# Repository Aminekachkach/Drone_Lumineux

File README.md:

[![Contributors][contributors-shield]][contributors-url]
[![LinkedIn][linkedin-shield]][linkedin-url]
[![LinkedIn2][linkedin-shield2]][linkedin-url2]

<!-- PROJECT LOGO -->
<br />
<div align="center">

<h3 align="center">Drone Lumineux</h3>

  <p align="center">
    A magic drone
</div>

<!-- TABLE OF CONTENTS -->
<details>
  <summary>Table des matières</summary>
  <ol>
    <li>
      <a href="#Introduction">Introduction</a>
      <ul>
        <li><a href="#organigramme-des-tâches-du-projet">Organigramme des tâches du projet</a </li>
        <li><a href="#architecture-générale">Architecture générale</a </li>
      </ul>
    </li>
    <li>
      <a href="#built-with">Build with</a>
    </li>
    <li>
      <a href="#test-initaire">Test Unitaire</a>
    <ul>
        </li><a href="#ESC">ESC</a></li>
        <li><a href="#MPU6050">MPU6050</a></li>
        <li><a href="#Neopixel">Neopixel</a></li>
    </ul>

  </ol>
</details>

## Introduction  
Le projet Drone Lumineux vise à concevoir un drone équipé d'un jeu de lumières. L'objectif est de créer une expérience visuelle unique en combinant les fonctionnalités d'un drone avec des effets lumineux spectaculaires.

Pour cela,  nous avons établi notre projet en utilisant une approche agile avec Scrum et les concepts d'épique (epic), de fonctionnalité (feature) et d'histoire utilisateur (user story). 

## Built With

* [![C][C.js]][C-url]
* [![Cube][Cube.js]][Cube-url]

### Organigramme des tâches du projet

En utilisant le modèle, nous avons identifié et défini les tâches qui correspondent aux histoires utilisateurs. L'objectif est de fournir rapidement de la valeur à notre produit en travaillant sur ces tâches de manière itérative. 
 
### Architecture générale

Après avoir effectué la sélection des composants et défini l'architecture générale de notre PCB , nous avons choisi d'utiliser deux contrôleurs différents : le microcontrôleur Nucleo STM32L412KB et le SoC QuickLogic Quick Feather EOS S3. L'objectif était de déterminer le contrôleur qui serait le plus adapté à notre configuration spécifique.
Cependant, lors du processus de développement, une mauvaise manipulation a entraîné un dysfonctionnement du bootloader du SoC, le rendant inutilisable (brické). Cette situation a nécessité d'abandonner l'utilisation du SoC Quick Feather EOS S3 pour notre projet.

[Drone_board_STM32_PCB](https://github.com/Aminekachkach/Drone_Lumineux/tree/main/hardware/Drone_board)

## Test Unitaire
Dans notre projet, nous utilisons des tests unitaires pour vérifier le bon fonctionnement de chaque composant, module et fonctionnalité du code. Les principaux éléments soumis à ces tests sont le driver ESC, le Nopixel et le MPU6050, ainsi que des fonctionnalités spécifiques telles que la configuration des broches PWM et la lecture des données du gyromètre.

### ESC

[Code Moteur](https://github.com/Aminekachkach/Drone_Lumineux/blob/main/firmware/drone/Core/Src/main_moteur.c)

Le driver ESC est spécifiquement conçu pour contrôler les moteurs brushless à courant continu (BLDC). Il reçoit en entrée un signal de modulation de largeur d'impulsion (PWM) qui permet de commander les phases du moteur. Dans notre application, nous utilisons des kits ESC+Moteurs fournis par miniplanes.

Sur le microcontrôleur Nucleo-STM32L412KB, nous allouons 4 broches qui sont connectées à la même chaîne PWM1 afin d'assurer la synchronisation.

PA8  ->  Broche PWM1-1

PA9  ->  Broche PWM1-2

PA10 ->  Broche PWM1-3

PA11 ->  Broche PWM1-4

Le driver fonctionne en configurant un signal PWM avec une période de 20 ms. Le rapport cyclique est ajusté pour envoyer des signaux de 1 ms pour l'initialisation, 1,5 ms pour une vitesse moyenne et 2 ms pour la vitesse maximale. Cela signifie qu'une variation de 1 ms à 2 ms fera tourner les moteurs de la vitesse minimale à la vitesse maximale.

Dans notre code, nous  générons les signaux PWM pour les 4 sorties, nous définissons trois constantes de vitesse : Rapport_cyclique_Min, Rapport_cyclique_securite et Rapport_cyclique_Max. À l'aide d'une boucle for, nous faisons varier la vitesse en utilisant les constantes Rapport_cyclique_Min et Rapport_cyclique_securite pour augmenter progressivement la vitesse des moteurs jusqu'à une vitesse raisonnable.

### MPU6050
[Code MPU](https://github.com/Aminekachkach/Drone_Lumineux/blob/main/firmware/drone/Core/Src/main_mpu.c)

Le MPU6050 est un composant qui combine un gyroscope et un accéléromètre à trois axes. Il est utilisé pour mesurer l'orientation, la rotation et l'accélération. Il utilise une communication I2C pour interagir avec notre microcontroleur STM32, nous allouons deux broches spécifiques pour établir la communication I2C avec les broches suivantes :

PA7  ->  Broche SCL

PB5  ->  Broche SDA

Au niveau du code, il existe une subtilité importante qui consiste à définir l'adresse du composant shiftée de 1 (0x68 << 1). Cela est nécessaire pour assurer une communication réussie entre le module et le microcontrôleur.

Avant de commencer la configuration, nous effectuons une vérification en interrogeant le registre "Who_am_i" à l'adresse 0x75. Cette étape nous permet de nous assurer que le module communique correctement avec le microcontrôleur. Si la communication est établie, le registre renverra la valeur 0x68.

Ensuite, nous procédons à la configuration de l'horloge interne à 8 MHz en utilisant le registre "Power management" situé à l'adresse 0x6B. Nous lui attribuons la valeur 0x00 pour sélectionner notre horloge souhaitée.

Nous appliquons également un filtre passe-bas avec une fréquence de coupure de 1 kHz afin d'éliminer les bruits qui pourraient perturber le fonctionnement du composant. Ce filtre est configuré en utilisant le registre situé à l'adresse 0x1A. Nous lui attribuons la valeur 0x05, ce qui correspond à une bande passante de 10 Hz.

Passons maintenant à la configuration du gyromètre en manipulant le registre "Gyro_Config" du MPU6050, situé à l'adresse 0x1B. Ce registre joue un rôle crucial dans la définition de la plage de mesure du gyromètre, qui est fixée à ± 500 °/s. Cette valeur détermine la projection maximale des mesures sur la plage d'acquisition du convertisseur analogique-numérique (ADC).

En ce qui concerne l'acquisition de données,  il faut prendre en compte la sensibilité du gyromètre, exprimée en LSB (Least Significant Bit) par degré par seconde (°/s). Pour notre plage de mesure de ± 500 °/s, la sensibilité est de 65.5 LSB/°/s comme indiqué sur la figure suivante :

Pour acquérir les données du gyromètre sur les trois axes X, Y et Z, nous devons effectuer une lecture de 6 octets consécutifs, commençant à l'adresse 0x43 et se terminant à l'adresse 0x48. Chaque axe nécessite 2 octets, donc en lisant les 6 octets, nous obtenons les mesures pour les trois axes.
La raison pour laquelle nous lisons ces 6 octets est que les données du gyromètre sont stockées dans des registres consécutifs, un registre pour chaque axe (X, Y et Z). Chaque registre contient 2 octets, qui représentent la valeur de mesure pour cet axe spécifique.

Une fois les données du gyromètre acquises, nous devons les ajuster en les divisant par la sensibilité mentionnée précédemment (65.5). Cette étape de correction permet d'obtenir des mesures précises en degrés par seconde, en prenant en considération la sensibilité spécifique du gyromètre.

### Neopixel

[Code Neopixel](https://github.com/Aminekachkach/Drone_Lumineux/tree/Neopixel)

Les LED WS2812  utilisent un protocole de modulation de largeur d'impulsion (Pulse Width Modulation - PWM) pour transmettre les informations de couleur et de luminosité. Dans ce protocole, la valeur d'un bit est déterminée par la durée d'une impulsion.

Pour les deux types de LED, les niveaux de timing à respecter pour encoder un "0" ou un "1" sont généralement les suivants :

Pour un "0" logique :

La durée de l'impulsion haute (HIGH) est généralement d'environ 0,35 μs.
La durée de l'impulsion basse (LOW) est généralement d'environ 0,8 μs.
Pour un "1" logique :

La durée de l'impulsion haute (HIGH) est généralement d'environ 0,7 μs.
La durée de l'impulsion basse (LOW) est généralement d'environ 0,6 μs.

Pour piloter, le Neopixel, nous avons utiliser un timer et DMA pour faire des déplecements de buffers.
Le code source provient d'un driver existant.

<!-- MARKDOWN LINKS & IMAGES -->
<!-- https://www.markdownguide.org/basic-syntax/#reference-style-links -->
[contributors-shield]:https://img.shields.io/badge/CONTRIBUTORS-2-green
[contributors-url]: https://github.com/Aminekachkach/Drone_Lumineux/graphs/contributors
[linkedin-shield]: https://img.shields.io/badge/-LinkedIn-black.svg?style=for-the-badge&logo=linkedin&colorB=555
[linkedin-url]: https://www.linkedin.com/in/amine-kachkach/
[linkedin-shield2]: https://img.shields.io/badge/-LinkedIn-black.svg?style=for-the-badge&logo=linkedin&colorB=555
[linkedin-url2]: https://www.linkedin.com/in/bilal-marecar/
[product-screenshot]: images/screenshot.png
[C.js]: https://img.shields.io/badge/LanguageC-darkblue
[C-url]: https://www.gnu.org/software/gnu-c-manual/gnu-c-manual.html
[Cube.js]: https://img.shields.io/badge/STM32Cube-lightblue
[Cube-url]: https://www.st.com/en/ecosystems/stm32cube.html/

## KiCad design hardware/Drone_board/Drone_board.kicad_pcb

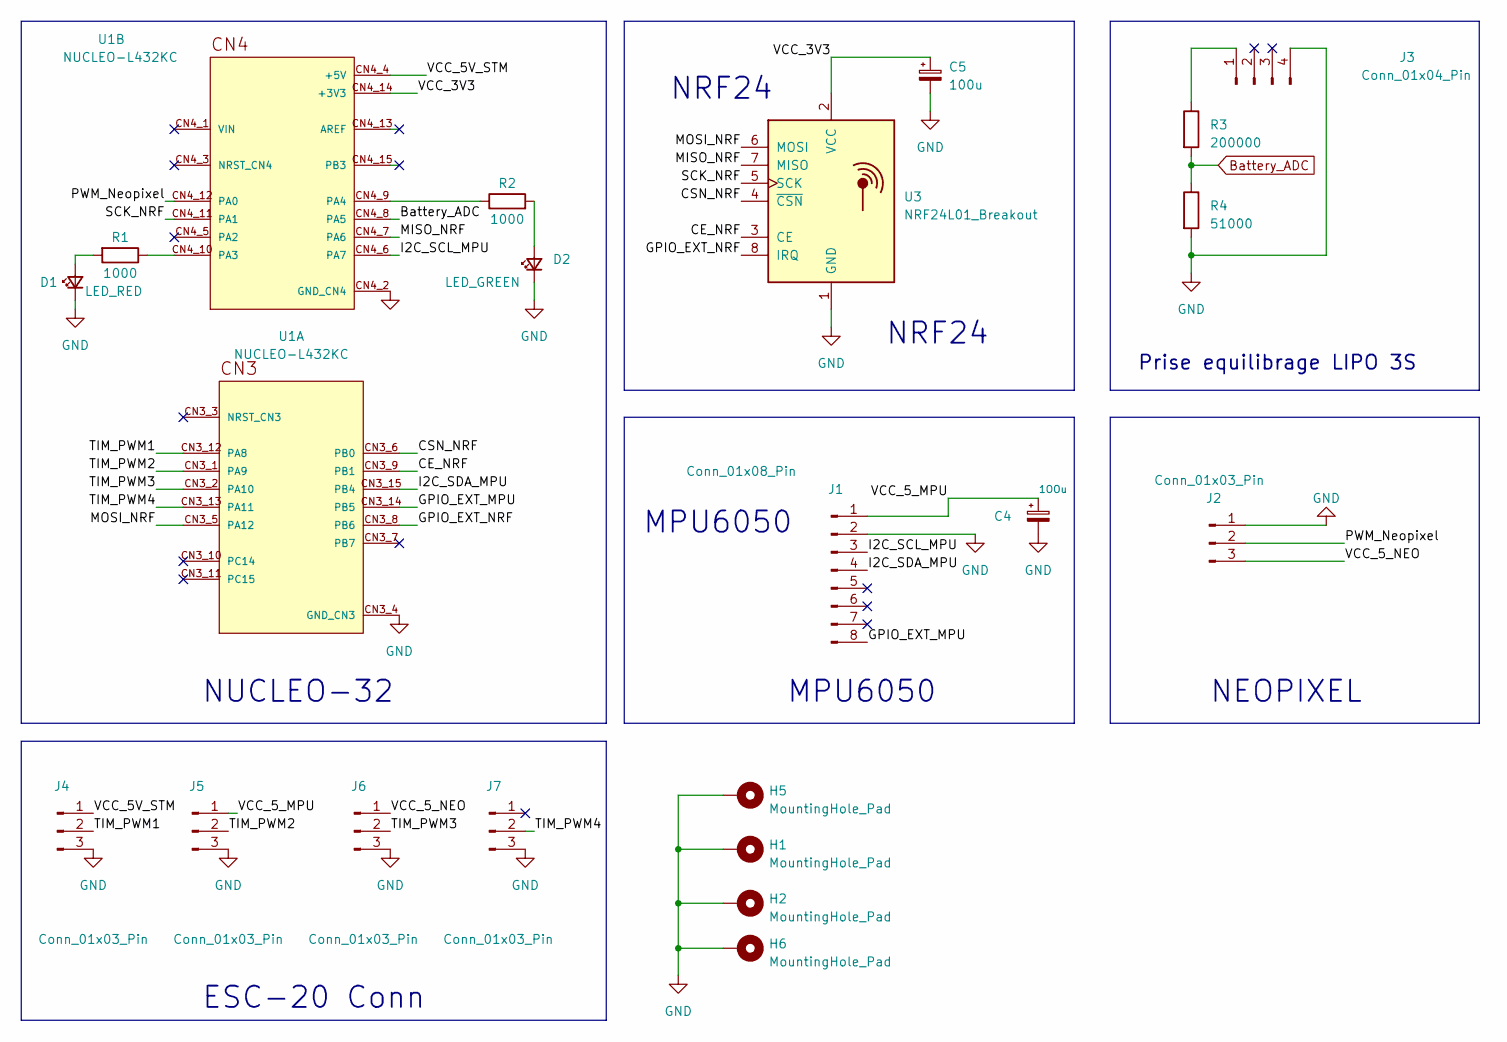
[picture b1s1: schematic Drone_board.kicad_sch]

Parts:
C4: 1OOu; CP_Elec_6.3x7.7
C5: 100u; CP_Elec_6.3x7.7
D1: LED_RED; LED_0603_1608Metric_Pad1.05x0.95mm_HandSolder
D2: LED_GREEN; LED_0603_1608Metric_Pad1.05x0.95mm_HandSolder
H1, H2, H5, H6: MountingHole_Pad; MountingHole_3.2mm_M3_Pad
J1: Conn_01x08_Pin; PinHeader_1x08_P2.54mm_Vertical
J2, J4, J5, J6, J7: Conn_01x03_Pin; PinHeader_1x03_P2.54mm_Vertical
J3: Conn_01x04_Pin; JST_XH_B4B-XH-A_1x04_P2.50mm_Vertical
R1, R2: 1000; R_0603_1608Metric
R3: 200000; R_0603_1608Metric
R4: 51000; R_0603_1608Metric
U1: NUCLEO-L432KC; MODULE_NUCLEO-L432KC; PARTREV N/A
U3: NRF24L01_Breakout; nRF24L01_Breakout

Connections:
/CE_NRF: U1.CN3_9 (PB1), U3.3 (CE)
/CSN_NRF: U1.CN3_6 (PB0), U3.4 (~CSN)
/GPIO_EXT_MPU: J1.8, U1.CN3_14 (PB5)
/GPIO_EXT_NRF: U1.CN3_8 (PB6), U3.8 (IRQ)
/I2C_SCL_MPU: J1.3, U1.CN4_6 (PA7)
/I2C_SDA_MPU: J1.4, U1.CN3_15 (PB4)
/MISO_NRF: U1.CN4_7 (PA6), U3.7 (MISO)
/MOSI_NRF: U1.CN3_5 (PA12), U3.6 (MOSI)
/PWM_Neopixel: J2.2, U1.CN4_12 (PA0)
/SCK_NRF: U1.CN4_11 (PA1), U3.5 (SCK)
/TIM_PWM1: J4.2, U1.CN3_12 (PA8)
/TIM_PWM2: J5.2, U1.CN3_1 (PA9)
/TIM_PWM3: J6.2, U1.CN3_2 (PA10)
/TIM_PWM4: J7.2, U1.CN3_13 (PA11)
/VCC_3V3: C5.1, U1.CN4_14 (+3V3), U3.2 (VCC)
/VCC_5V_STM: J4.1, U1.CN4_4 (+5V)
/VCC_5_MPU: C4.1, J1.1, J5.1
/VCC_5_NEO: J2.3, J6.1
Battery_ADC: R3.2, R4.1, U1.CN4_8 (PA5)
GND: C4.2, C5.2, D1.1 (K), D2.1 (K), H1.1, H2.1, H5.1, H6.1, J1.2, J2.1, J3.4, J4.3, J5.3, J6.3, J7.3, R4.2, U1.CN3_4 (GND_CN3), U1.CN4_2 (GND_CN4), U3.1 (GND)
unnamed: D1.2 (A), R1.2
unnamed: D2.2 (A), R2.2
unnamed: J3.1, R3.1
unnamed: R1.1, U1.CN4_10 (PA3)
unnamed: R2.1, U1.CN4_9 (PA4)

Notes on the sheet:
NRF24
NUCLEO-32
NEOPIXEL
MPU6050
ESC-20 Conn
NRF24
MPU6050
Prise equilibrage LIPO 3S

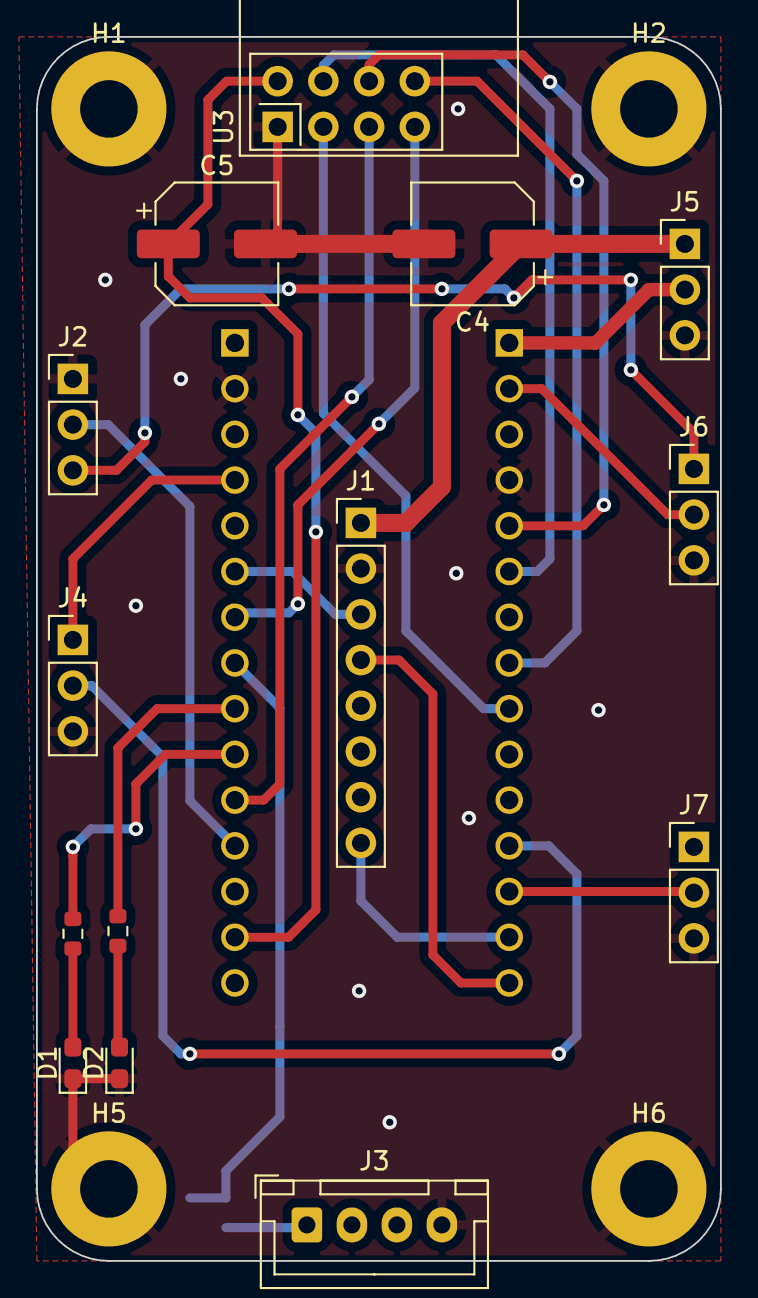
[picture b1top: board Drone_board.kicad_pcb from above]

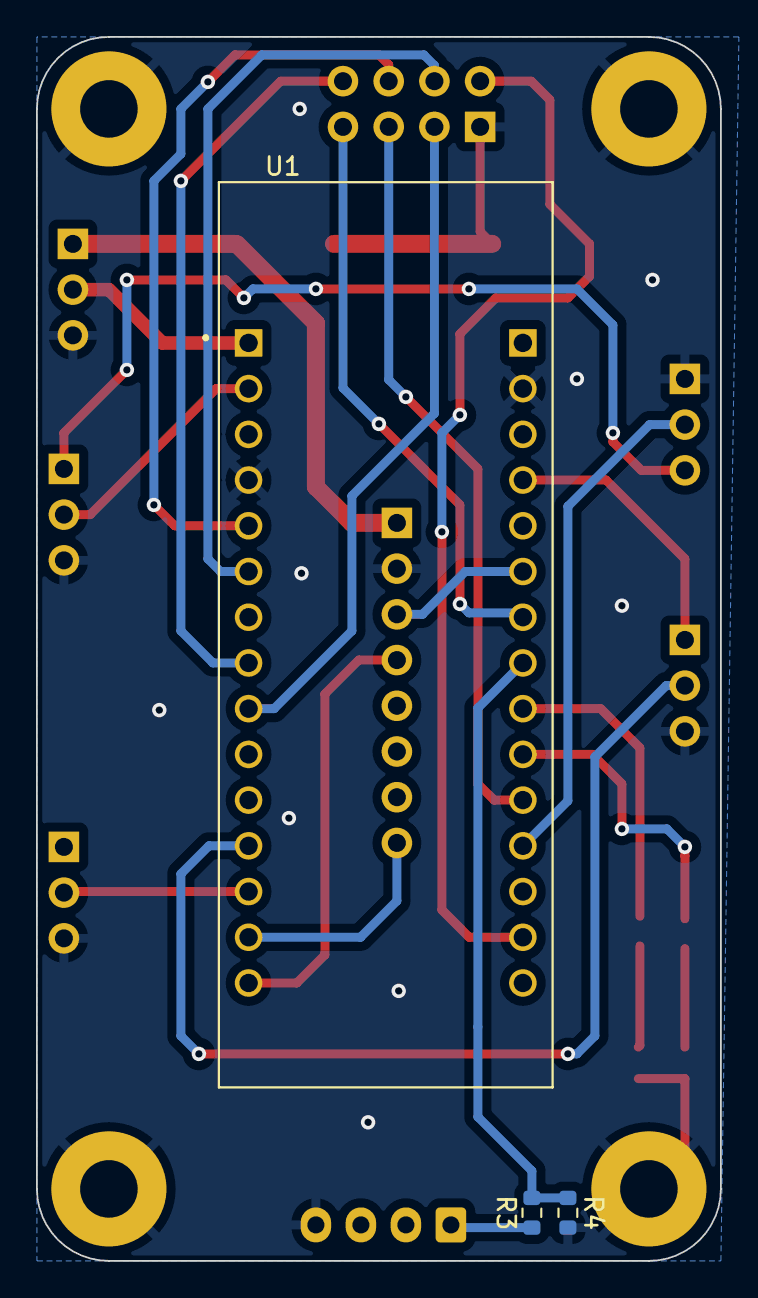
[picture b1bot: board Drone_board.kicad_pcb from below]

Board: 2 copper layers, 38.0 x 68.0 mm, 21 parts (3 on the bottom side), 25 nets.

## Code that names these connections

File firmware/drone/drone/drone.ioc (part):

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Mcu.Name=STM32L412KBUx
Mcu.Package=UFQFPN32
Mcu.UserName=STM32L412KBUx
PA0-CK_IN.GPIOParameters=GPIO_Label
PA0-CK_IN.GPIO_Label=PWM_Neopixel
PA0-CK_IN.Signal=S_TIM2_CH1
PA1.GPIOParameters=GPIO_Label
PA1.GPIO_Label=SCK_NRF
PA1.Mode=Full_Duplex_Master
PA1.Signal=SPI1_SCK
PA10.GPIOParameters=GPIO_Label
PA10.GPIO_Label=TIM_PWM3
PA10.Signal=S_TIM1_CH3
PA11.GPIOParameters=GPIO_Label
PA11.GPIO_Label=TIM_PWM4
PA11.Signal=S_TIM1_CH4
PA12.GPIOParameters=GPIO_Label
PA12.GPIO_Label=MOSI_NRF
PA12.Mode=Full_Duplex_Master
PA12.Signal=SPI1_MOSI
PA13\ (JTMS/SWDIO).GPIOParameters=GPIO_Label
PA13\ (JTMS/SWDIO).GPIO_Label=SWDIO
PA13\ (JTMS/SWDIO).Mode=Serial_Wire
PA13\ (JTMS/SWDIO).Signal=SYS_JTMS-SWDIO
PA14\ (JTCK/SWCLK).GPIOParameters=GPIO_Label
PA14\ (JTCK/SWCLK).GPIO_Label=SWCLK
PA14\ (JTCK/SWCLK).Mode=Serial_Wire
PA14\ (JTCK/SWCLK).Signal=SYS_JTCK-SWCLK
PA15\ (JTDI).GPIOParameters=GPIO_Label
PA15\ (JTDI).GPIO_Label=VCP_RX
PA15\ (JTDI).Mode=Asynchronous
PA15\ (JTDI).Signal=USART2_RX
PA2.GPIOParameters=GPIO_Label
PA2.GPIO_Label=VCP_TX
PA2.Mode=Asynchronous
PA2.Signal=USART2_TX
PA3.GPIOParameters=GPIO_Label
PA3.GPIO_Label=LED_RED
PA3.Signal=GPIO_Output
PA4.GPIOParameters=GPIO_Label
PA4.GPIO_Label=LED_GREEN
PA4.Signal=GPIO_Output
PA5.GPIOParameters=GPIO_Label
PA5.GPIO_Label=Battery_ADC
PA5.Signal=ADCx_IN10
PA6.GPIOParameters=GPIO_Label
PA6.GPIO_Label=MISO_NRF
PA6.Mode=Full_Duplex_Master
PA6.Signal=SPI1_MISO
PA7.GPIOParameters=GPIO_Label
PA7.GPIO_Label=I2C_SCL_MPU
PA7.Mode=I2C
PA7.Signal=I2C3_SCL
PA8.GPIOParameters=GPIO_Label
PA8.GPIO_Label=TIM_PWM1
PA8.Signal=S_TIM1_CH1
PA9.GPIOParameters=GPIO_Label
PA9.GPIO_Label=TIM_PWM2
PA9.Signal=S_TIM1_CH2
PB0.GPIOParameters=GPIO_Label
PB0.GPIO_Label=CSN_NRF
PB0.Signal=GPIO_Output
PB1.GPIOParameters=GPIO_Label
PB1.GPIO_Label=CE_NRF
PB1.Signal=GPIO_Output
PB3\ (JTDO/TRACESWO).GPIOParameters=GPIO_Speed,GPIO_Label
PB3\ (JTDO/TRACESWO).GPIO_Label=LD3 [Green]
PB3\ (JTDO/TRACESWO).GPIO_Speed=GPIO_SPEED_FREQ_LOW
PB3\ (JTDO/TRACESWO).Signal=GPIO_Output
PB4\ (NJTRST).Mode=I2C
PB4\ (NJTRST).Signal=I2C3_SDA
PB5.GPIOParameters=GPIO_Label
PB5.GPIO_Label=GPIO_EXT_MPU
PB5.Signal=GPXTI5
PB6.GPIOParameters=GPIO_Label
PB6.GPIO_Label=GPIO_EXT_NRF
PB6.Signal=GPXTI6
PC14-OSC32_IN\ (PC14).Mode=LSE-External-Oscillator
PC14-OSC32_IN\ (PC14).Signal=RCC_OSC32_IN
PC15-OSC32_OUT\ (PC15).Mode=LSE-External-Oscillator
PC15-OSC32_OUT\ (PC15).Signal=RCC_OSC32_OUT
RCC.HSE_VALUE=8000000
RCC.SYSCLKFreq_VALUE=80000000
RCC.SYSCLKSource=RCC_SYSCLKSOURCE_PLLCLK
board=NUCLEO-L412KB
boardIOC=true

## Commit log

2023-03-09 Datasheets
2023-03-11 Removed directory
2023-03-23 Hardware_datasheets
2023-03-23 Documentation
2023-04-07 Board Drone
2023-04-10 Schematic drone for validation
2023-04-13 Deleted a file from git
2023-04-13 Board schematic validate
2023-04-19 PCB Footprint
2023-05-10 Update PCB
2023-05-13 Neopixel blink
2023-05-24 PCB validated by refrent
2023-05-25 ESC motor driver
2023-05-29 ESC unit test
2023-05-29 Readme
2023-06-15 Update driver motor
2023-06-23 Create test
2023-06-23 amine push
2023-06-23 amine push with neopixel main
2023-06-23 uncommented mpu
